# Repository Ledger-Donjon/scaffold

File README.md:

# Scaffold

When performing hardware security evaluation of integrated circuits and embedded
platforms, the first step is to setup the device to be able to automate tests,
retrieve results and trigger instruments to perform measurements or inject
faults. Scaffold is an electronic motherboard designed to quickly setup,
instrument and test cirtcuits. The board can be controlled through USB using a
Python3 API, enabling easy development of tests. All the project is
Open-Hardware and Open-Source.

The FPGA architecture runs at 100 MHz and embeds many peripherals:

- 2 x UART,
- I2C (master),
- ISO7816 (master),
- ISO14443-A (NFC daughterboard)
- SPI (master),
- Power supply controllers for each evaluation socket,
- 4 x Delay and pulse generators with 10 ns resolution
- 2 x chaining modules for advanced triggering
- Clock generator with glitching feature
- And more to come in the future!

The board also integrates an 11X analog amplifier with 200 MHz bandwidth for
power measurement. The on-board shunt resistor can be tuned from 0 to
100 Ohms.

Scaffold is able to operate from 1.5V to 3.3V devices: power supplies and I/O
bank voltage can be tuned thanks to adjustable voltage regulators. Scaffold can
be powered from USB or external power supplies.

Four special I/Os can generate 5V pulses, which are compatible with
*ALPhANOV PDM* laser sources (50 Ohm TTL).

## Getting the board

All the files required to fabricate the board are included in the repository.
If you do not wish to build it yourself, you can request for quotation by
sending a mail to scaffold@ledger.fr (only for Europe or USA shipping).

## Installation

Python3 library can be installed using pip:

    pip3 install donjon-scaffold

## Documentation

API documentation is available on [Read the Docs](https://donjonscaffold.readthedocs.io).

## Licensing

Scaffold is released under GNU Lesser General Public Licence version 3 (LGPLv3).
See COPYING and COPYING.LESSER for license details.

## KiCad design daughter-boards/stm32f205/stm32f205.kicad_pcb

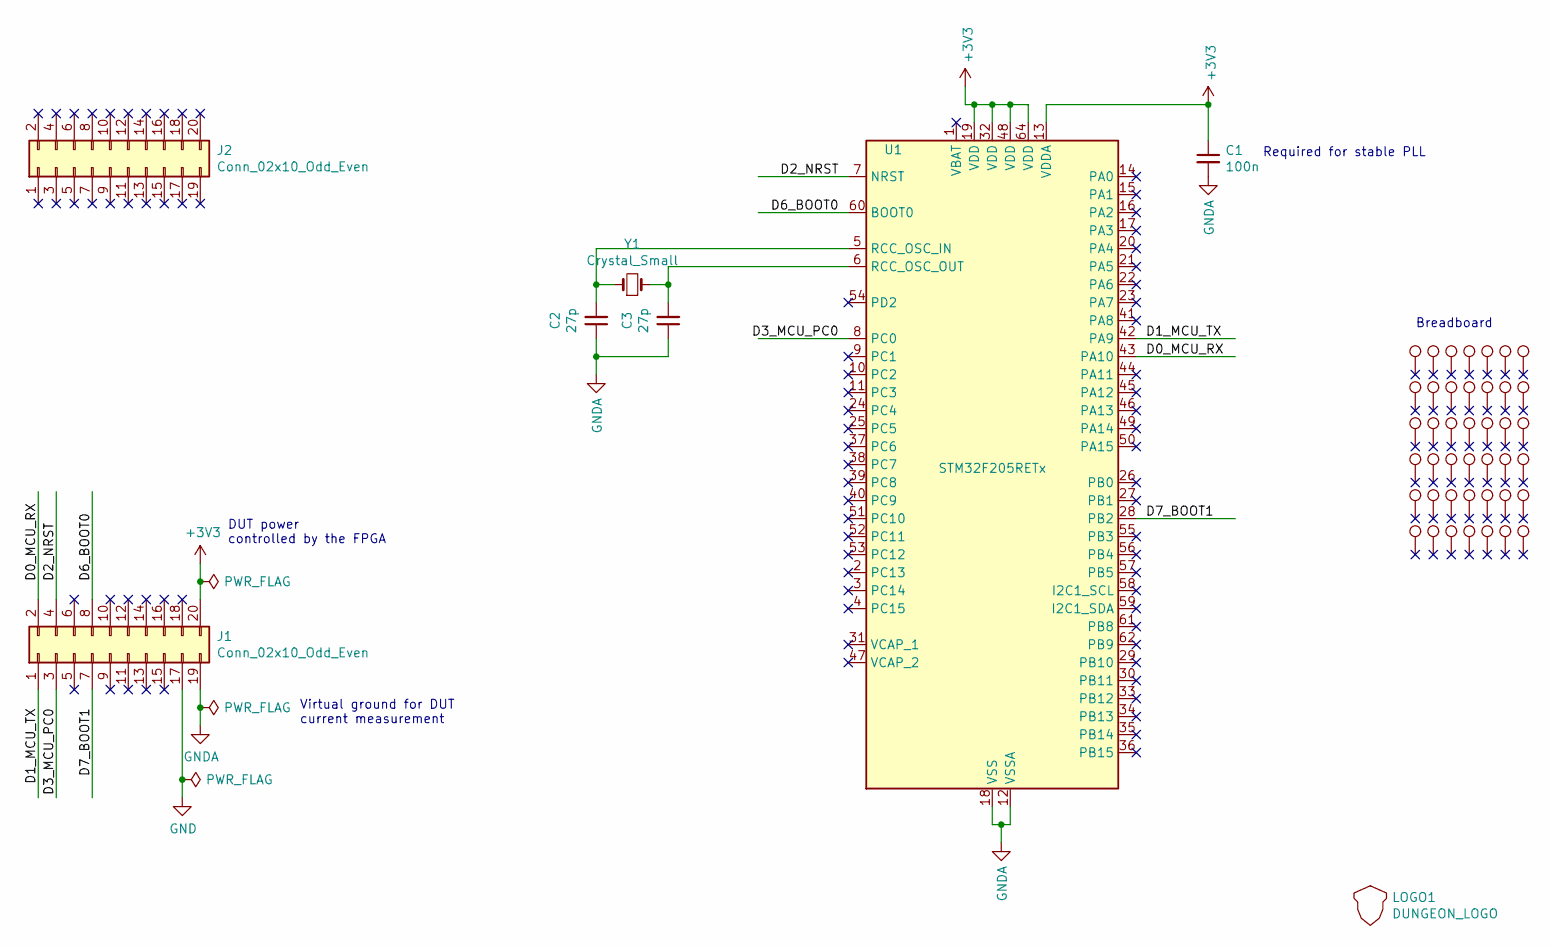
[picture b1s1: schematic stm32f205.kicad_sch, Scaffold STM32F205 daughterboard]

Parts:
C1: 100n; C_0805_2012Metric
C2, C3: 27p; C_0805_2012Metric
J1, J2: Conn_02x10_Odd_Even; PinSocket_2x10_P2.54mm_Vertical
LOGO1: DUNGEON_LOGO; donjon-2000
TP1, TP2, TP3, TP4, TP5, TP6, TP7, TP8, TP9, TP10, TP11, TP12, TP13, TP14, TP15, TP16, TP17, TP18, TP19, TP20, TP21, TP22, TP23, TP24, TP25, TP26, TP27, TP28, TP29, TP30, TP31, TP32, TP33, TP34, TP35, TP36, TP37, TP38, TP39, TP40, TP41, TP42: TestPoint; TEST_BREADBOARD_RECTANGULAR
U1: STM32F205RETx; ALLSOCKET-QFP64
Y1: Crystal_Small; Crystal_HC18-U_Vertical

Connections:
+3V3: C1.1, J1.20, U1.13 (VDDA), U1.19 (VDD), U1.32 (VDD), U1.48 (VDD), U1.64 (VDD)
/D0_MCU_RX: J1.2, U1.43 (PA10)
/D1_MCU_TX: J1.1, U1.42 (PA9)
/D2_NRST: J1.4, U1.7 (NRST)
/D3_MCU_PC0: J1.3, U1.8 (PC0)
/D6_BOOT0: J1.8, U1.60 (BOOT0)
/D7_BOOT1: J1.7, U1.28 (PB2)
GND: J1.17
GNDA: C1.2, C2.1, C3.1, J1.19, U1.12 (VSSA), U1.18 (VSS), U1.63 (VSS)
unnamed: C2.2, U1.5 (RCC_OSC_IN), Y1.1
unnamed: C3.2, U1.6 (RCC_OSC_OUT), Y1.2

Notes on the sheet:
Breadboard
Virtual ground for DUT current measurement
Required for stable PLL
DUT power controlled by the FPGA

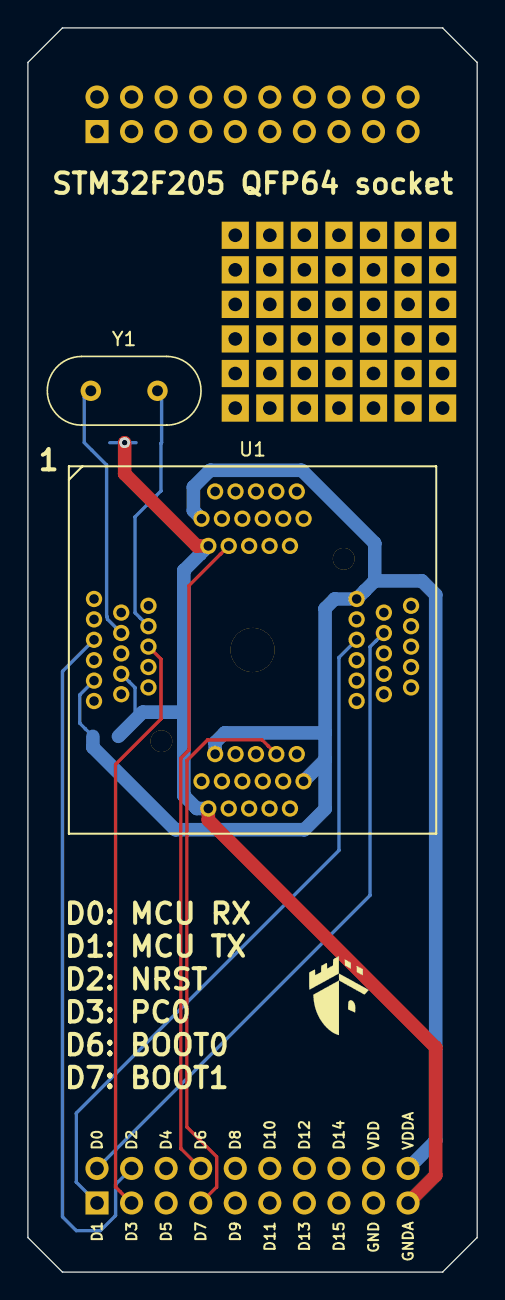
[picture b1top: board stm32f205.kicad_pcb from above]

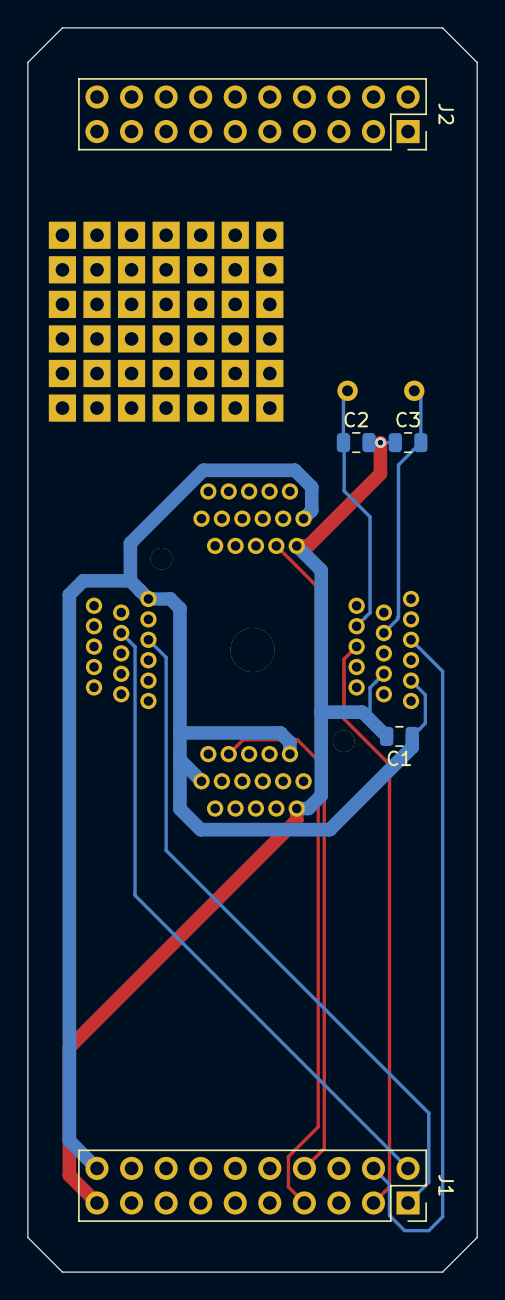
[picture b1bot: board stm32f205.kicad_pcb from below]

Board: 2 copper layers, 33.0 x 91.4 mm, 50 parts (5 on the bottom side), 10 nets.

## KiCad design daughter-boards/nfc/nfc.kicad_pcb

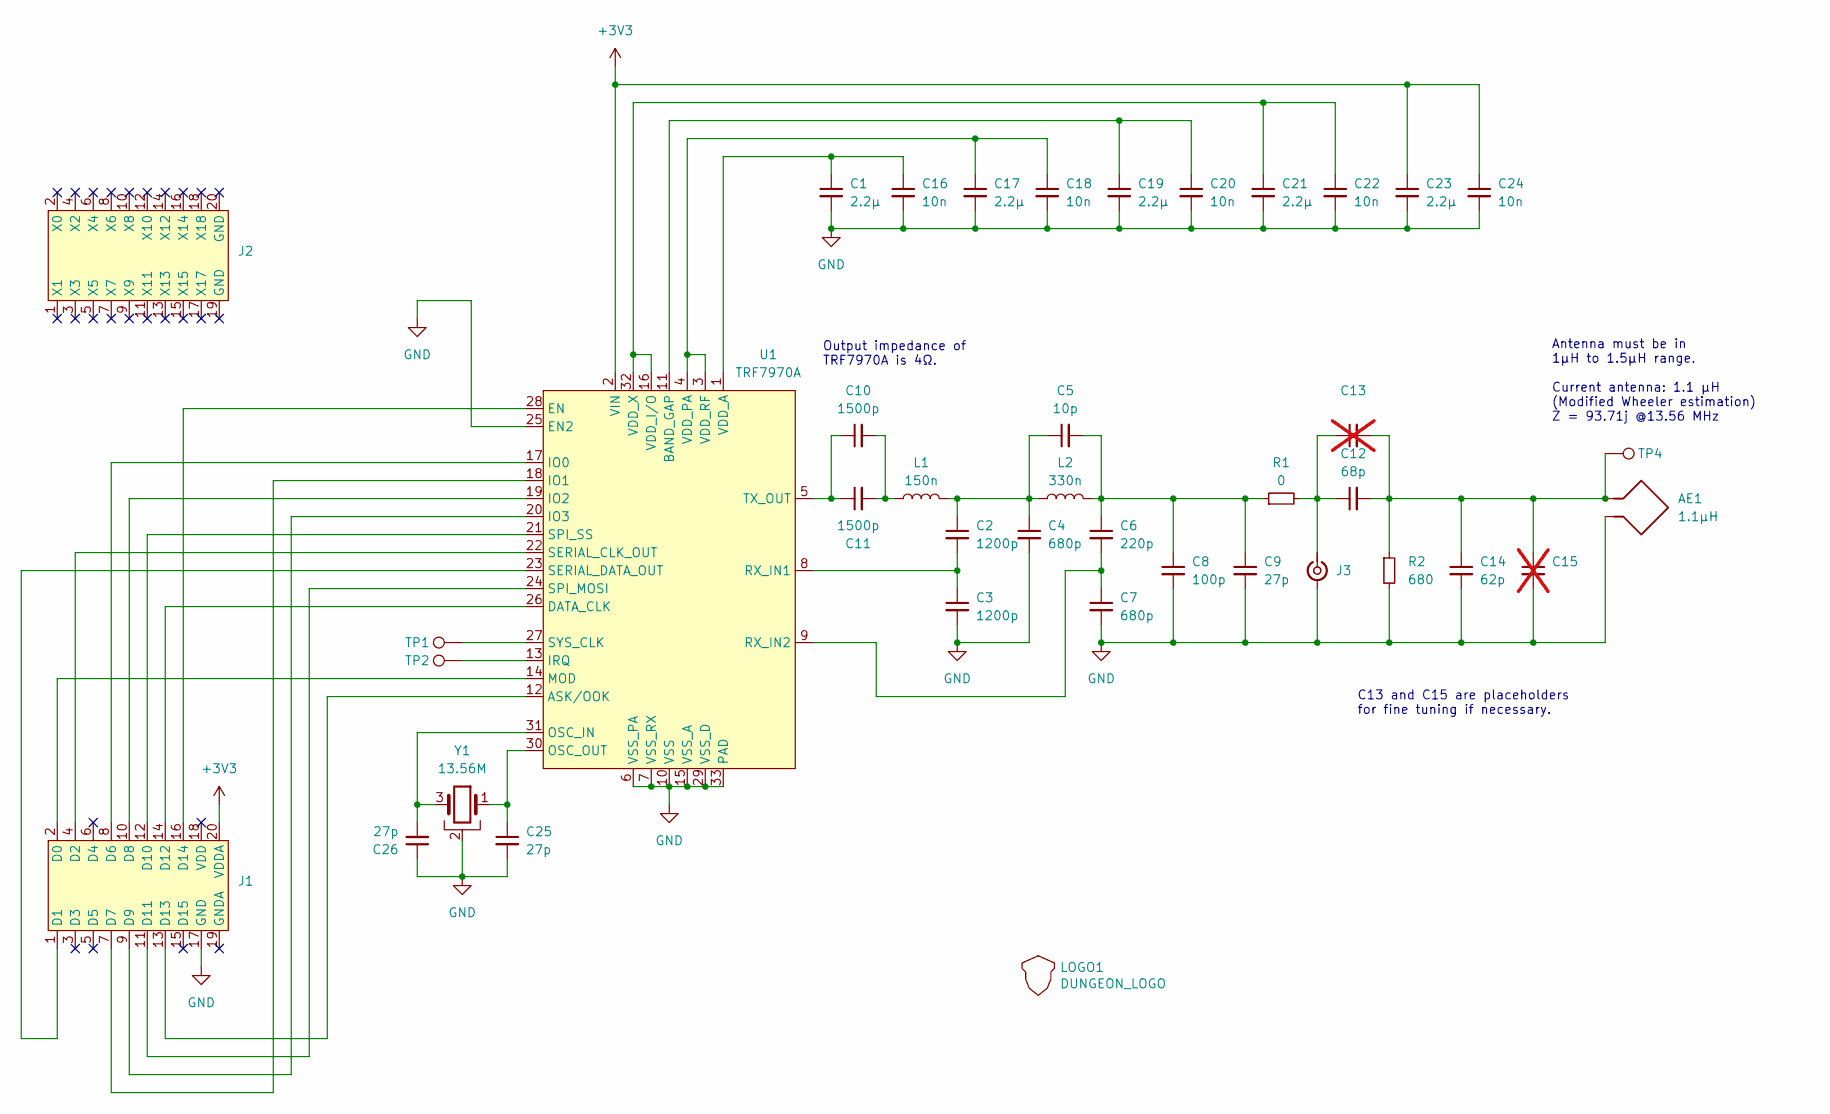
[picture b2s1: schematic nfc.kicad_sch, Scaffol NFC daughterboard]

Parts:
AE1: 1.1µH; ANTENNA
C1, C17, C19, C21, C23: 2.2µ; C_0603_1608Metric
C2, C3: 1200p; C_0603_1608Metric
C4, C7: 680p; C_0603_1608Metric
C5: 10p; C_0603_1608Metric
C6: 220p; C_0603_1608Metric
C8: 100p; C_0603_1608Metric
C9, C25, C26: 27p; C_0603_1608Metric
C10, C11: 1500p; C_0603_1608Metric
C12: 68p; C_0603_1608Metric
C13, C15: C_0603_1608Metric; not fitted
C14: 62p; C_0603_1608Metric
C16, C18, C20, C22, C24: 10n; C_0603_1608Metric
J1, J2: PinSocket_2x10_P2.54mm_Vertical
J3: Conn_Coaxial_Small; U.FL_Molex_MCRF_73412-0110_Vertical
L1: 150n; L_0603_1608Metric
L2: 330n; L_0603_1608Metric
LOGO1: DUNGEON_LOGO; donjon-2000
R1: 0; R_0603_1608Metric
R2: 680; R_0603_1608Metric
TP1, TP2, TP4: TestPoint; TestPoint_Pad_D1.0mm
U1: TRF7970A; QFN-32-1EP_5x5mm_P0.5mm_EP3.45x3.45mm
Y1: 13.56M; Crystal_SMD_Abracon_ABM8G-4Pin_3.2x2.5mm

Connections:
+3V3: C23.1, C24.1, J1.20 (VDDA), U1.2 (VIN)
GND: AE1.2, C1.2, C3.2, C4.2, C7.2, C8.2, C9.2, C14.2, C15.2, C16.2, C17.2, C18.2, C19.2, C20.2, C21.2, C22.2, C23.2, C24.2, C25.2, C26.1, J1.17 (GND), J3.2 (Ext), R2.2, U1.6 (VSS_PA), U1.7 (VSS_RX), U1.10 (VSS), U1.15 (VSS_A), U1.25 (EN2), U1.29 (VSS_D), U1.33 (PAD), Y1.2
unnamed: AE1.1, C12.2, C13.2, C14.1, C15.1, R2.1, TP4.1
unnamed: C2.1, C4.1, C5.1, L1.2, L2.1
unnamed: C5.2, C6.1, C8.1, C9.1, L2.2, R1.1
unnamed: C10.2, C11.2, L1.1
unnamed: J1.2 (D0), U1.14 (MOD)
unnamed: J1.1 (D1), U1.23 (SERIAL_DATA_OUT)
unnamed: J1.4 (D2), U1.22 (SERIAL_CLK_OUT)
unnamed: J1.8 (D6), U1.17 (IO0)
unnamed: J1.7 (D7), U1.18 (IO1)
unnamed: J1.10 (D8), U1.19 (IO2)
unnamed: J1.9 (D9), U1.20 (IO3)
unnamed: J1.12 (D10), U1.21 (SPI_SS)
unnamed: J1.11 (D11), U1.24 (SPI_MOSI)
unnamed: J1.14 (D12), U1.26 (DATA_CLK)
unnamed: J1.13 (D13), U1.12 (ASK/OOK)
unnamed: J1.16 (D14), U1.28 (EN)
unnamed: C12.1, C13.1, J3.1 (In), R1.2
unnamed: C19.1, C20.1, U1.11 (BAND_GAP)
unnamed: TP2.1, U1.13 (IRQ)
unnamed: C26.2, U1.31 (OSC_IN), Y1.3
unnamed: C25.1, U1.30 (OSC_OUT), Y1.1
unnamed: C2.2, C3.1, U1.8 (RX_IN1)
unnamed: C6.2, C7.1, U1.9 (RX_IN2)
unnamed: TP1.1, U1.27 (SYS_CLK)
unnamed: C10.1, C11.1, U1.5 (TX_OUT)
unnamed: C1.1, C16.1, U1.1 (VDD_A)
unnamed: C21.1, C22.1, U1.16 (VDD_I/O), U1.32 (VDD_X)
unnamed: C17.1, C18.1, U1.3 (VDD_RF), U1.4 (VDD_PA)

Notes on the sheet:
Antenna must be in 1µH to 1.5µH range. Current antenna: 1.1 µH (Modified Wheeler estimation) Z = 93.71j @13.56 MHz
Output impedance of TRF7970A is 4Ω.
C13 and C15 are placeholders for fine tuning if necessary.

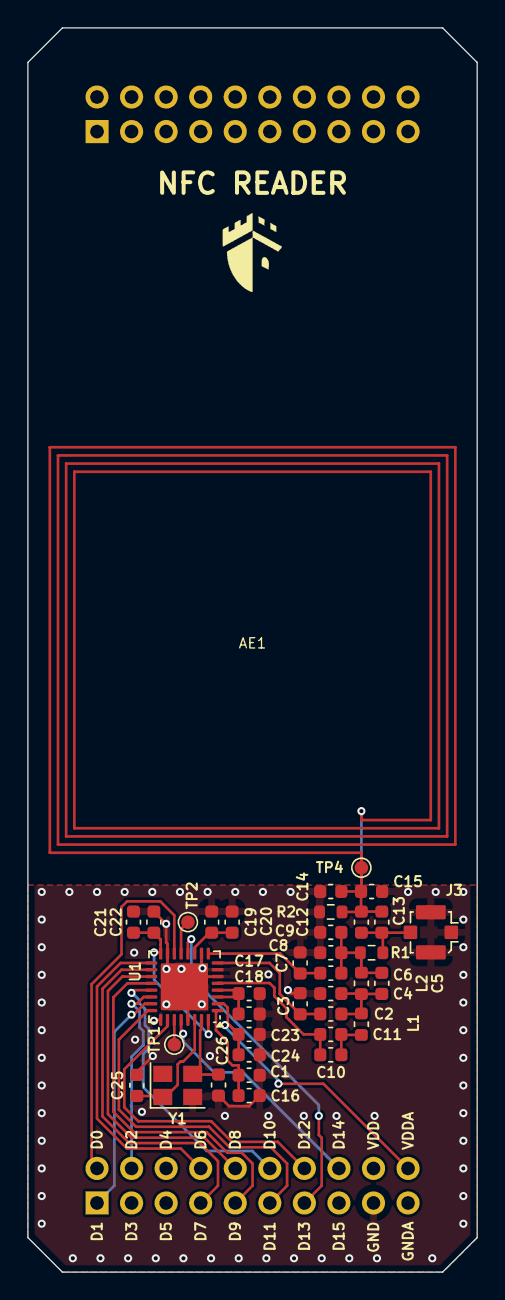
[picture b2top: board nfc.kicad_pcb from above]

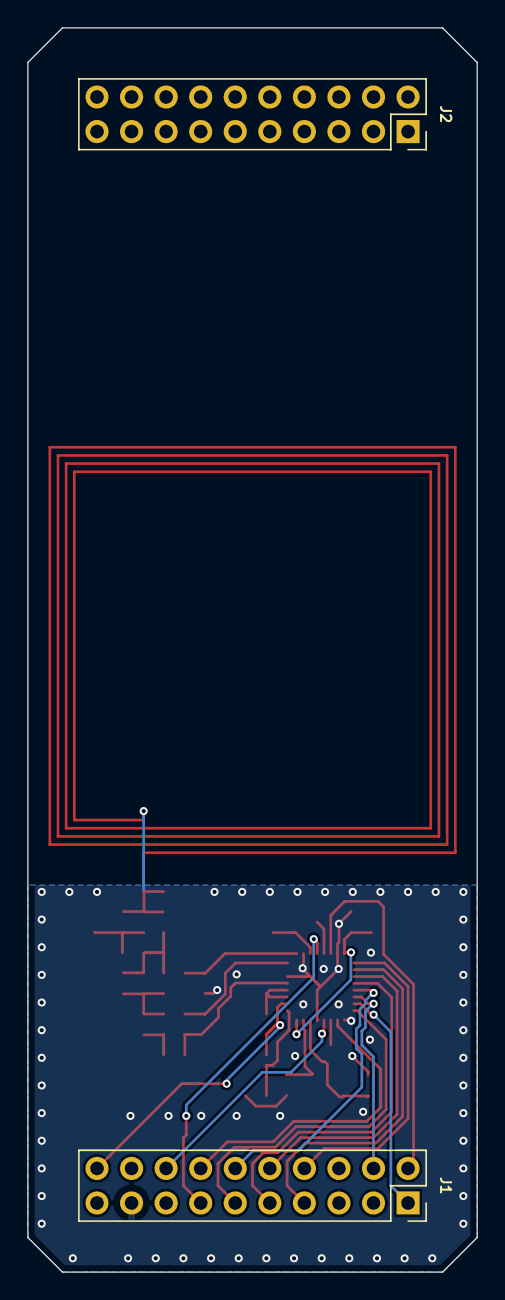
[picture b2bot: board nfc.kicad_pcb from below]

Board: 2 copper layers, 33.0 x 91.4 mm, 40 parts (2 on the bottom side), 30 nets.

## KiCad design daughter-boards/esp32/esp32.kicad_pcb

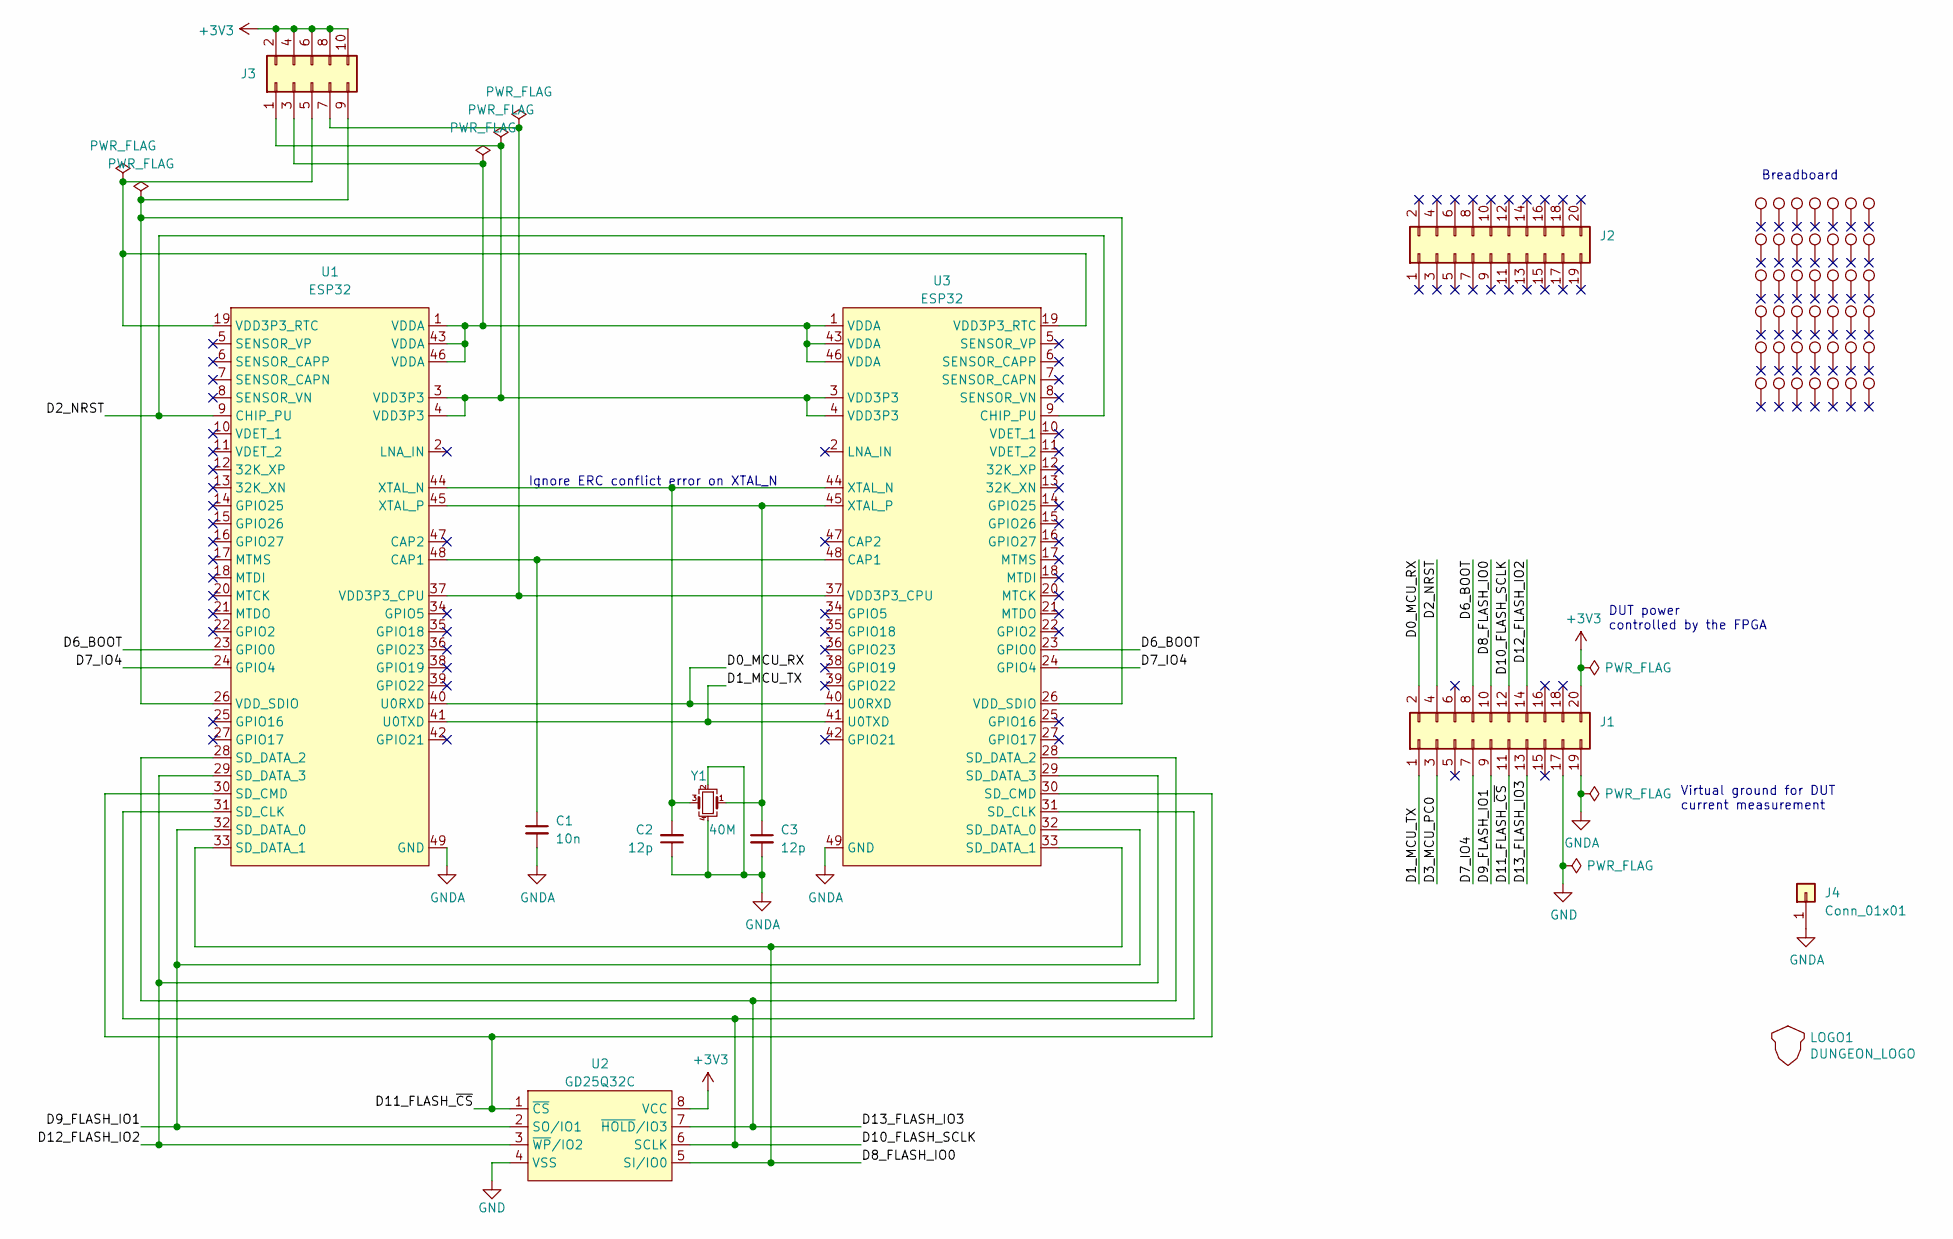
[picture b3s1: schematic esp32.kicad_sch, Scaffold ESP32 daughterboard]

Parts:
C1: 10n; C_0603_1608Metric
C2, C3: 12p; C_0603_1608Metric
J1, J2: Conn_02x10_Odd_Even; PinSocket_2x10_P2.54mm_Vertical
J3: Conn_02x05_Odd_Even; PinHeader_2x05_P2.54mm_Vertical
J4: Conn_01x01; PinHeader_1x01_P2.54mm_Vertical
LOGO1: DUNGEON_LOGO; donjon-2000
TP1, TP2, TP3, TP4, TP5, TP6, TP7, TP8, TP9, TP10, TP11, TP12, TP13, TP14, TP15, TP16, TP17, TP18, TP19, TP20, TP21, TP22, TP23, TP24, TP25, TP26, TP27, TP28, TP29, TP30, TP31, TP32, TP33, TP34, TP35, TP36, TP37, TP38, TP39, TP40, TP41, TP42: TestPoint; TEST_BREADBOARD_RECTANGULAR
U1, U3: ESP32; QFN-48-1EP_6x6mm_P0.4mm_EP4.3x4.3mm
U2: GD25Q32C; SOP-8_5.28x5.23mm_P1.27mm
Y1: 40M; Crystal_SMD_2520-4Pin_2.5x2.0mm

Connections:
+3V3: J1.20, J3.2, J3.4, J3.6, J3.8, J3.10, U2.8 (VCC)
/D0_MCU_RX: J1.2, U1.40 (U0RXD), U3.40 (U0RXD)
/D1_MCU_TX: J1.1, U1.41 (U0TXD), U3.41 (U0TXD)
/D2_NRST: J1.4, U1.9 (CHIP_PU), U3.9 (CHIP_PU)
/D3_MCU_PC0: J1.3
/D6_BOOT: J1.8, U1.23 (GPIO0), U3.23 (GPIO0)
/D7_IO4: J1.7, U1.24 (GPIO4), U3.24 (GPIO4)
/D8_FLASH_IO0: J1.10, U1.33 (SD_DATA_1), U2.5 (SI/IO0), U3.33 (SD_DATA_1)
/D9_FLASH_IO1: J1.9, U1.32 (SD_DATA_0), U2.2 (SO/IO1), U3.32 (SD_DATA_0)
/D10_FLASH_SCLK: J1.12, U1.31 (SD_CLK), U2.6 (SCLK), U3.31 (SD_CLK)
/D11_FLASH_~CS: J1.11, U1.30 (SD_CMD), U2.1 (~CS), U3.30 (SD_CMD)
/D12_FLASH_IO2: J1.14, U1.29 (SD_DATA_3), U2.3 (~WP~/IO2), U3.29 (SD_DATA_3)
/D13_FLASH_IO3: J1.13, U1.28 (SD_DATA_2), U2.7 (~HOLD~/IO3), U3.28 (SD_DATA_2)
GND: J1.17, U2.4 (VSS)
GNDA: C1.2, C2.1, C3.2, J1.19, J4.1, U1.49 (GND), U3.49 (GND), Y1.2, Y1.4
unnamed: C1.1, U1.48 (CAP1), U3.48 (CAP1)
unnamed: C2.2, U1.44 (XTAL_N), U3.44 (XTAL_N), Y1.3
unnamed: C3.1, U1.45 (XTAL_P), U3.45 (XTAL_P), Y1.1
unnamed: J3.1, U1.3 (VDD3P3), U1.4 (VDD3P3), U3.3 (VDD3P3), U3.4 (VDD3P3)
unnamed: J3.3, U1.1 (VDDA), U1.43 (VDDA), U1.46 (VDDA), U3.1 (VDDA), U3.43 (VDDA), U3.46 (VDDA)
unnamed: J3.5, U1.19 (VDD3P3_RTC), U3.19 (VDD3P3_RTC)
unnamed: J3.7, U1.37 (VDD3P3_CPU), U3.37 (VDD3P3_CPU)
unnamed: J3.9, U1.26 (VDD_SDIO), U3.26 (VDD_SDIO)

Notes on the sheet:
Ignore ERC conflict error on XTAL_N
DUT power controlled by the FPGA
Virtual ground for DUT current measurement
Breadboard

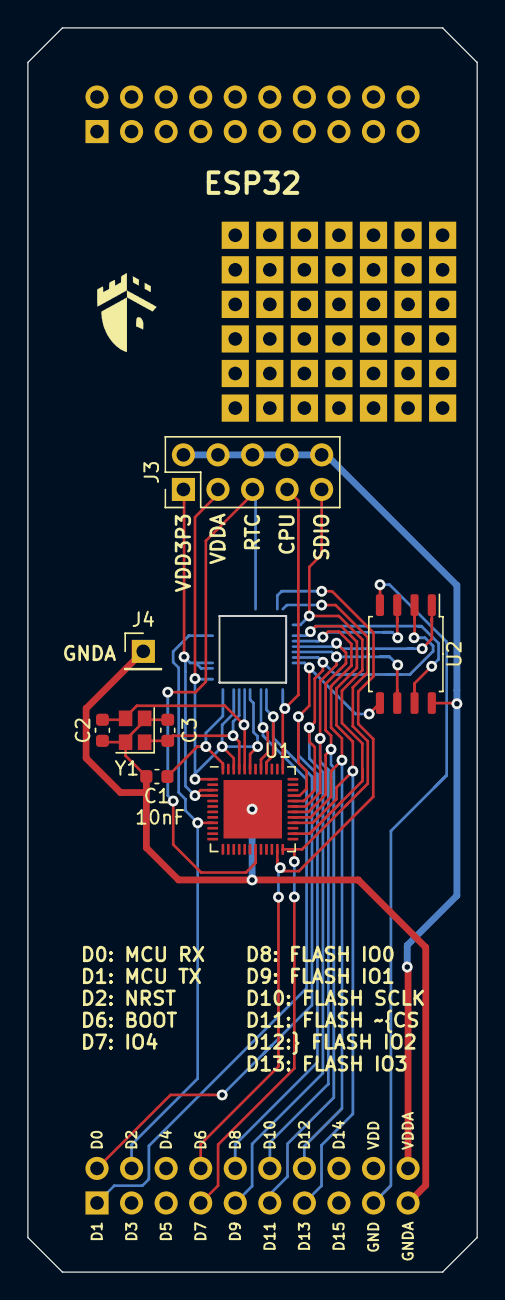
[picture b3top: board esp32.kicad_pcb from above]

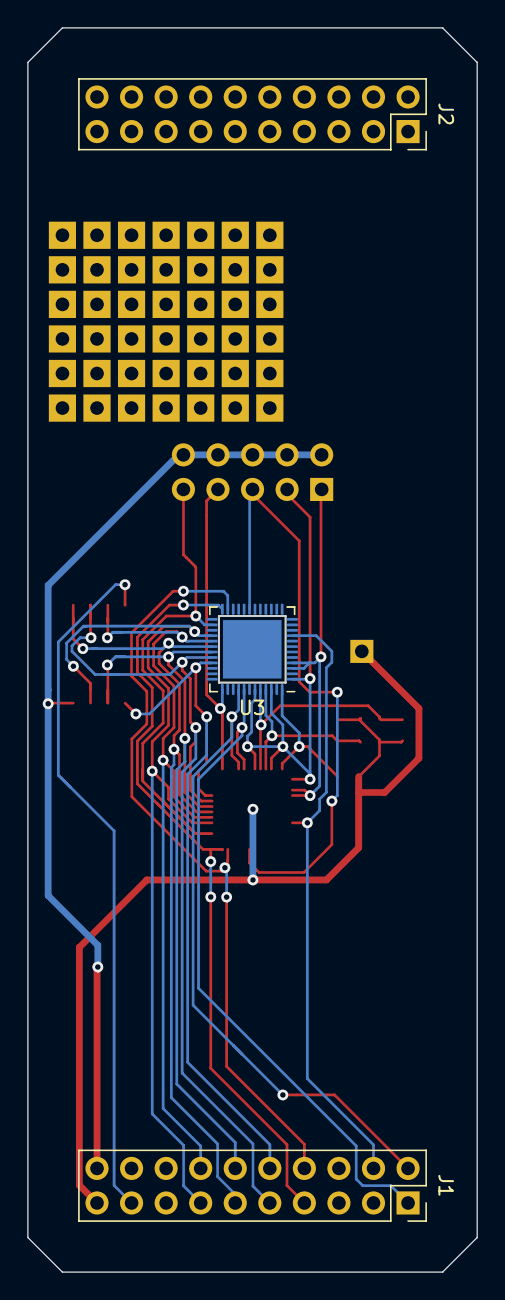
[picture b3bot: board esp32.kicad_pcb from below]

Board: 2 copper layers, 33.0 x 91.4 mm, 54 parts (3 on the bottom side), 22 nets.

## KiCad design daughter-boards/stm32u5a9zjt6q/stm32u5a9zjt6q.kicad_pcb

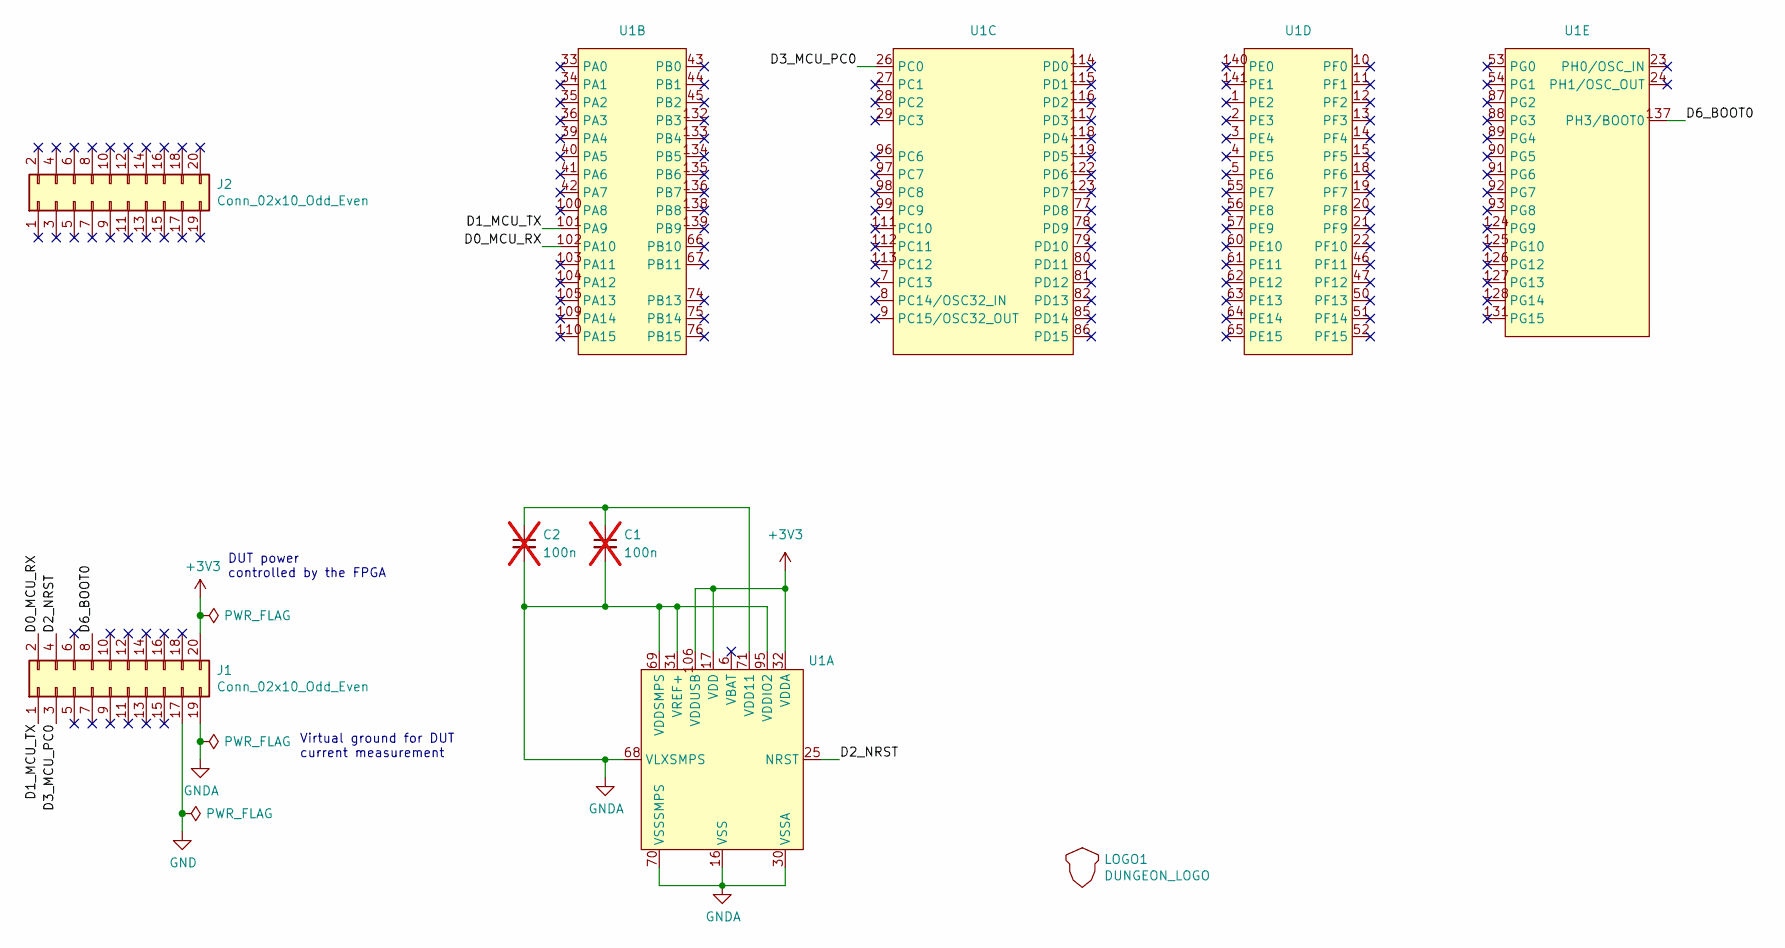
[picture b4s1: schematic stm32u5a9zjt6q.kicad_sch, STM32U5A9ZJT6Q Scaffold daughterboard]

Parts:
C1, C2: 100n; C_0603_1608Metric; not fitted
J1, J2: Conn_02x10_Odd_Even; PinSocket_2x10_P2.54mm_Vertical
LOGO1: DUNGEON_LOGO; donjon-2000
U1: LQFP-144_20x20mm_P0.5mm

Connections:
+3V3: J1.20, U1.17 (VDD), U1.32 (VDDA), U1.38 (VDD), U1.49 (VDD), U1.59 (VDD), U1.73 (VDD), U1.84 (VDD), U1.106 (VDDUSB), U1.108 (VDD), U1.121 (VDD), U1.144 (VDD)
/D0_MCU_RX: J1.2, U1.102 (PA10)
/D1_MCU_TX: J1.1, U1.101 (PA9)
/D2_NRST: J1.4, U1.25 (NRST)
/D3_MCU_PC0: J1.3, U1.26 (PC0)
/D6_BOOT0: J1.8, U1.137 (PH3/BOOT0)
GND: J1.17
GNDA: C1.2, C2.2, J1.19, U1.16 (VSS), U1.30 (VSSA), U1.31 (VREF+), U1.37 (VSS), U1.48 (VSS), U1.58 (VSS), U1.68 (VLXSMPS), U1.69 (VDDSMPS), U1.70 (VSSSMPS), U1.72 (VSS), U1.83 (VSS), U1.94 (VSS), U1.95 (VDDIO2), U1.107 (VSS), U1.120 (VSS), U1.129 (VSS), U1.130 (VDDIO2), U1.143 (VSS)
unnamed: C1.1, C2.1, U1.71 (VDD11), U1.142 (VDD11)

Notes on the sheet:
Virtual ground for DUT current measurement
DUT power controlled by the FPGA

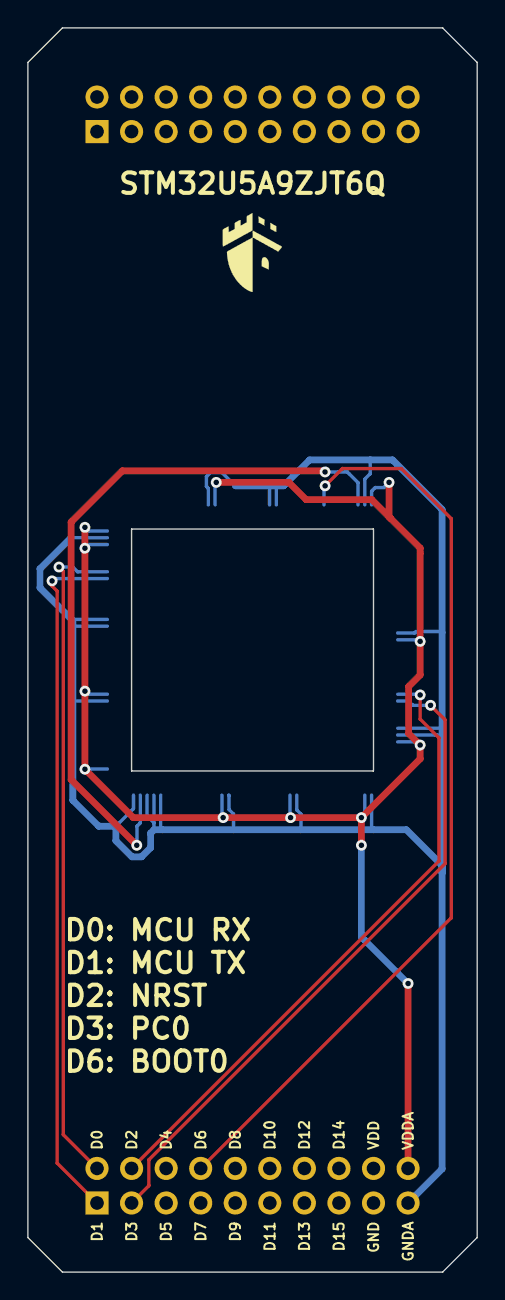
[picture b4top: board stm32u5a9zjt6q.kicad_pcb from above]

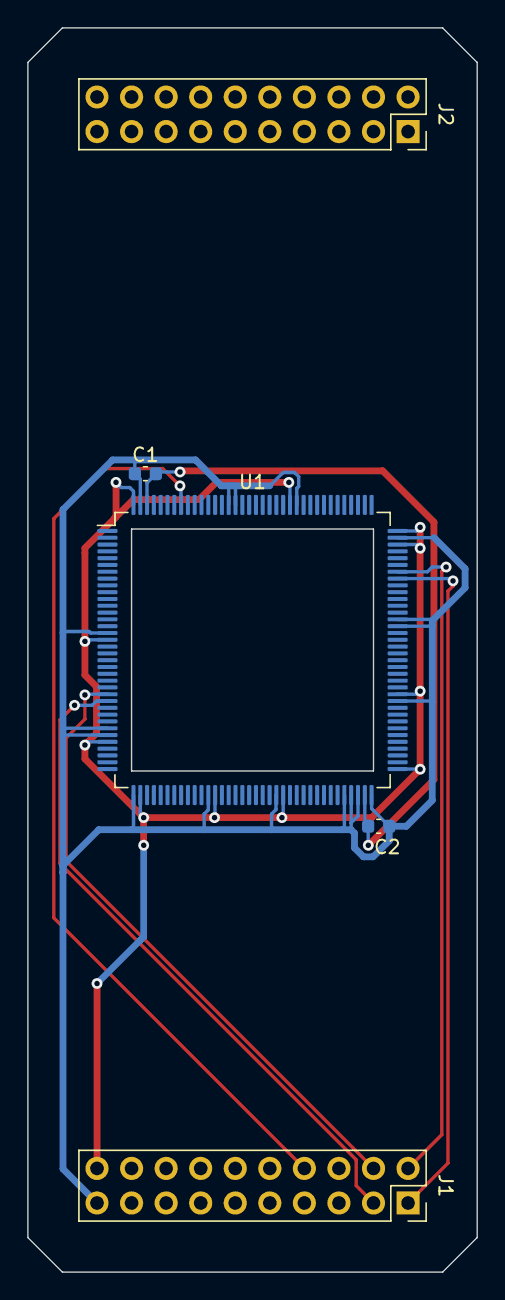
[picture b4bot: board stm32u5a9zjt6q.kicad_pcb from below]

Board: 2 copper layers, 33.0 x 91.4 mm, 6 parts (5 on the bottom side), 8 nets.

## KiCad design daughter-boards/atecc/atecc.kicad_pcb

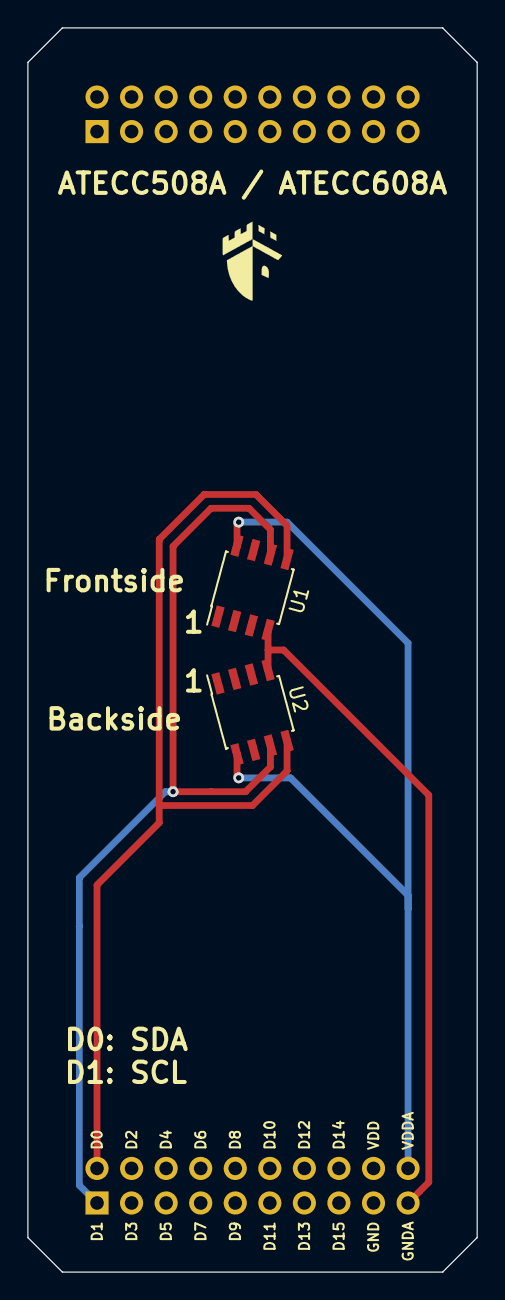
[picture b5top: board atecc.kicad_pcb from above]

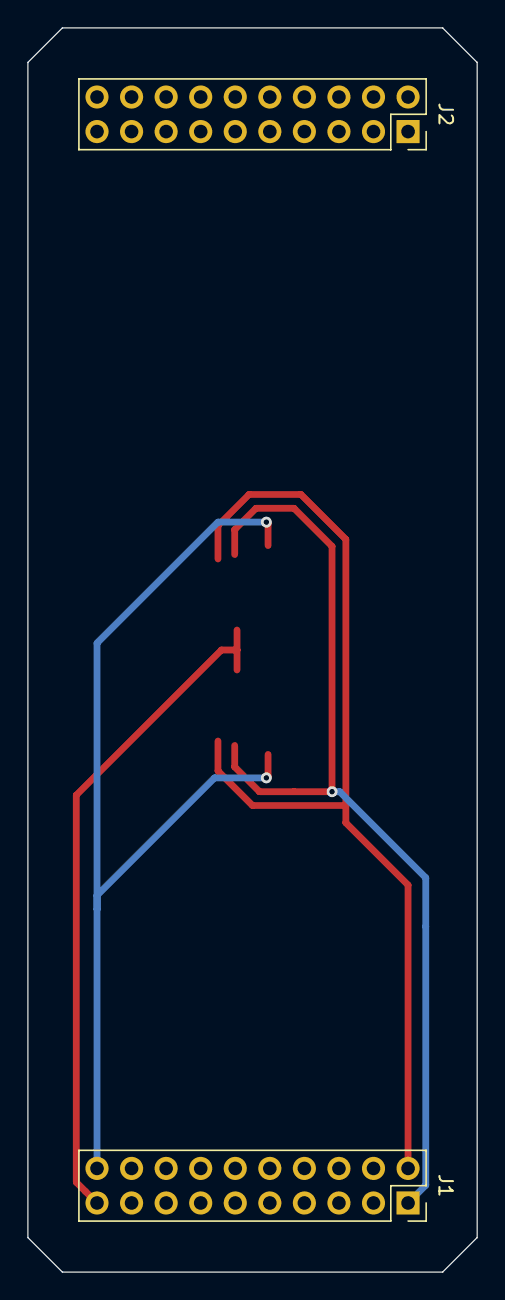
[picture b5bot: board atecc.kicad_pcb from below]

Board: 2 copper layers, 33.0 x 91.4 mm, 5 parts (2 on the bottom side), 4 nets.

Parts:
J1, J2: Conn_02x10_Odd_Even; PinSocket_2x10_P2.54mm_Vertical
LOGO1: DUNGEON_LOGO; donjon-2000
U1: ATECC508A; SOIC-8_3.9x4.9mm_P1.27mm
U2: ATECC508A; FLIP-SOIC-8_3.9x4.9mm_P1.27mm

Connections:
/D0: J1.2, U1.5, U2.5
/D1: J1.1, U1.6, U2.6
GNDA: J1.19, U1.4, U2.4
VDDA: J1.20, U1.8, U2.8

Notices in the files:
daughter-boards/atecc/atecc.kicad_pcb:
Under LGPL v3 license
